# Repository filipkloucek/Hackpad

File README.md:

# Hackpad

- Just followed hackclub's guided tutorial. It was really fun. Looking forward to make my own stuff :)

/ update // added a few extra things. Prolly gonna use this for Spotify

/ update 2 // Completely new design - realised i used a wrong display. But it looks even better now
  
/ firmware made by AI for now. I can'T code but gonna learn that too. 

Used parts: 

- 5x Cherry MX Switches
- 1x SK6812 MINI Led
- 1x XIAO RP2040
- 5x Blank DSA Keycaps
- 4x M3x16 Bolt
- 4x M3 Heatset
- 1x EC11 Rotary encoder
- 1x 0.91 inch OLED display (SDD1306 OLED) 

Files: 

- KMK Firmware (main.py) 
- HACKPAD V3 (HACKPAD - BOTTOM - V3,HACKPAD - TOP - V3,HACKPAD - PCB - V3)

PCB

SCHEMATIC

CASE

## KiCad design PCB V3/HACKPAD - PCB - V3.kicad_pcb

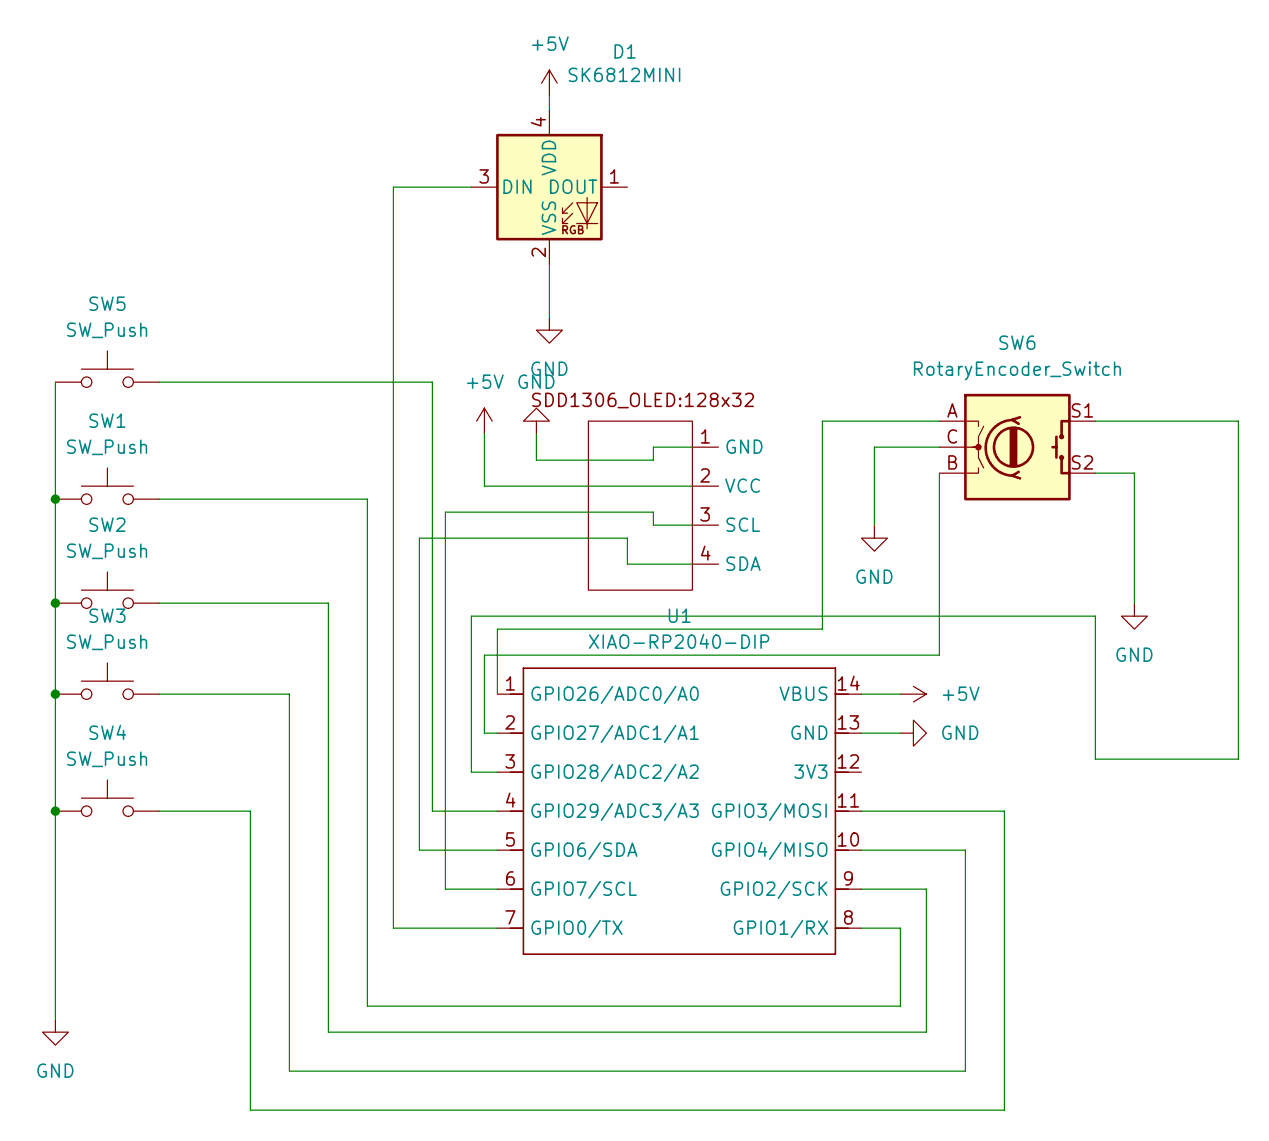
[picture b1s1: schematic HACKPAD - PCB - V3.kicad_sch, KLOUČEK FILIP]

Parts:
D1: SK6812MINI; LED_SK6812MINI_PLCC4_3.5x3.5mm_P1.75mm
DS1: SSD1306-0.91-OLED-4pin-128x32
SW1, SW2, SW3, SW4, SW5: SW_Push; SW_Cherry_MX_1.00u_PCB
SW6: RotaryEncoder_Switch; RotaryEncoder_Alps_EC11E-Switch_Vertical_H20mm
U1: XIAO-RP2040-DIP; MOUDLE14P-XIAO-DIP-SMD

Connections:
+5V: D1.4 (VDD), DS1.2 (VCC), U1.14 (VBUS)
GND: D1.2 (VSS), DS1.1 (GND), SW1.1, SW2.1, SW3.1, SW4.1, SW5.1, SW6.C, SW6.S2, U1.13 (GND)
unnamed: D1.3 (DIN), U1.7 (GPIO0/TX)
unnamed: DS1.3 (SCL), U1.6 (GPIO7/SCL)
unnamed: DS1.4 (SDA), U1.5 (GPIO6/SDA)
unnamed: SW1.2, U1.8 (GPIO1/RX)
unnamed: SW2.2, U1.9 (GPIO2/SCK)
unnamed: SW4.2, U1.11 (GPIO3/MOSI)
unnamed: SW3.2, U1.10 (GPIO4/MISO)
unnamed: SW6.A, U1.1 (GPIO26/ADC0/A0)
unnamed: SW6.B, U1.2 (GPIO27/ADC1/A1)
unnamed: SW6.S1, U1.3 (GPIO28/ADC2/A2)
unnamed: SW5.2, U1.4 (GPIO29/ADC3/A3)

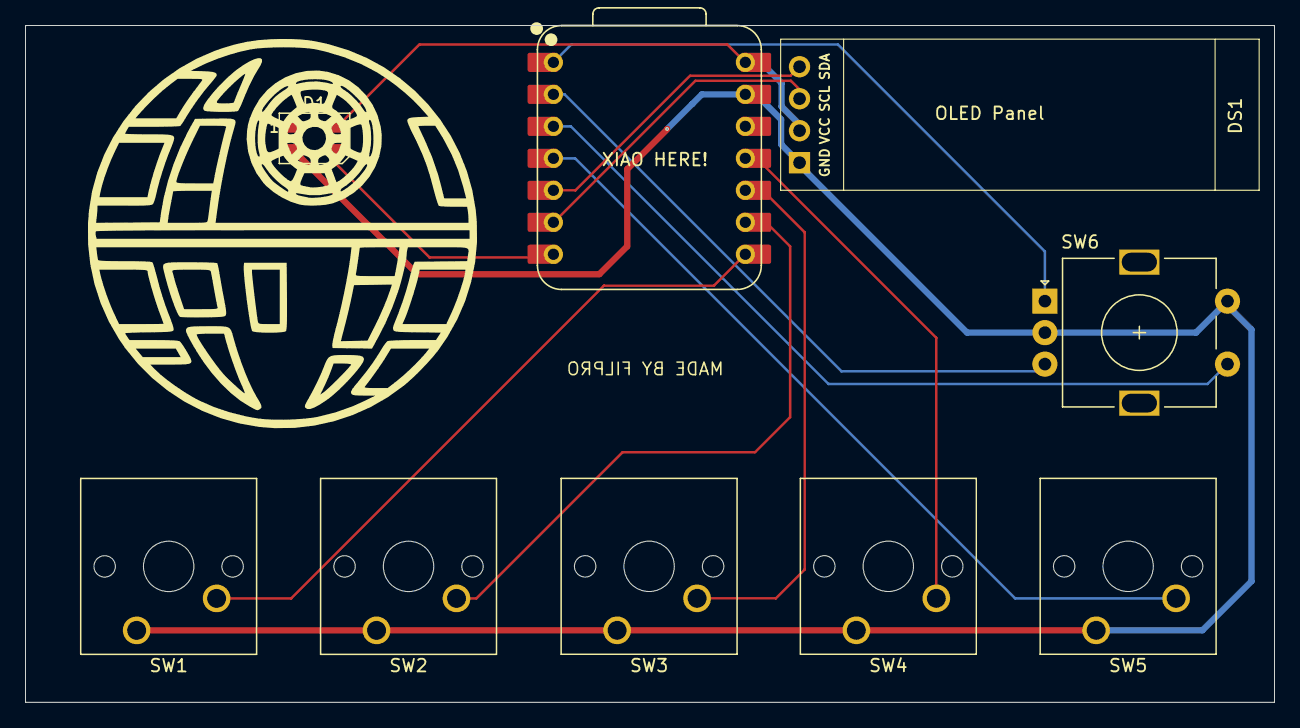
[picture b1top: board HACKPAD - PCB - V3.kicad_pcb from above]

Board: 2 copper layers, 99.2 x 53.7 mm, 10 parts (0 on the bottom side), 13 nets.

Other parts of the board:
D: LOGO

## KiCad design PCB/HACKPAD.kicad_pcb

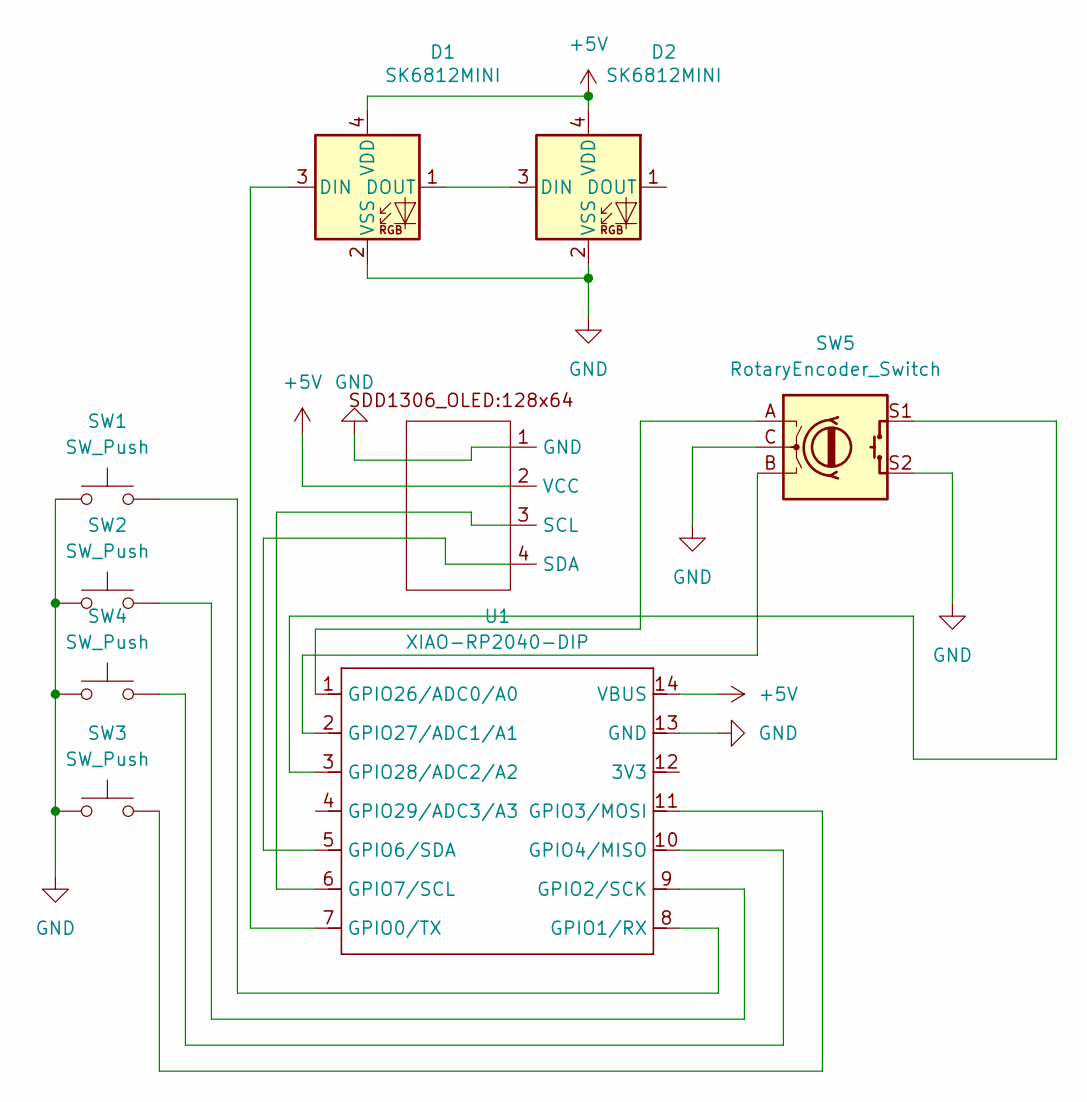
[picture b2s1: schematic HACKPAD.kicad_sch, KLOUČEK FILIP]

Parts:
D1, D2: SK6812MINI; LED_SK6812MINI_PLCC4_3.5x3.5mm_P1.75mm
DS1: 128x64OLED
SW1, SW2, SW3, SW4: SW_Push; SW_Cherry_MX_1.00u_PCB
SW5: RotaryEncoder_Switch; RotaryEncoder_Alps_EC11E-Switch_Vertical_H20mm
U1: XIAO-RP2040-DIP; MOUDLE14P-XIAO-DIP-SMD

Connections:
+5V: D1.4 (VDD), D2.4 (VDD), DS1.2 (VCC), U1.14 (VBUS)
GND: D1.2 (VSS), D2.2 (VSS), DS1.1 (GND), SW1.1, SW2.1, SW3.1, SW4.1, SW5.C, SW5.S2, U1.13 (GND)
unnamed: D1.3 (DIN), U1.7 (GPIO0/TX)
unnamed: D1.1 (DOUT), D2.3 (DIN)
unnamed: DS1.3 (SCL), U1.6 (GPIO7/SCL)
unnamed: DS1.4 (SDA), U1.5 (GPIO6/SDA)
unnamed: SW1.2, U1.8 (GPIO1/RX)
unnamed: SW2.2, U1.9 (GPIO2/SCK)
unnamed: SW3.2, U1.11 (GPIO3/MOSI)
unnamed: SW4.2, U1.10 (GPIO4/MISO)
unnamed: SW5.A, U1.1 (GPIO26/ADC0/A0)
unnamed: SW5.B, U1.2 (GPIO27/ADC1/A1)
unnamed: SW5.S1, U1.3 (GPIO28/ADC2/A2)

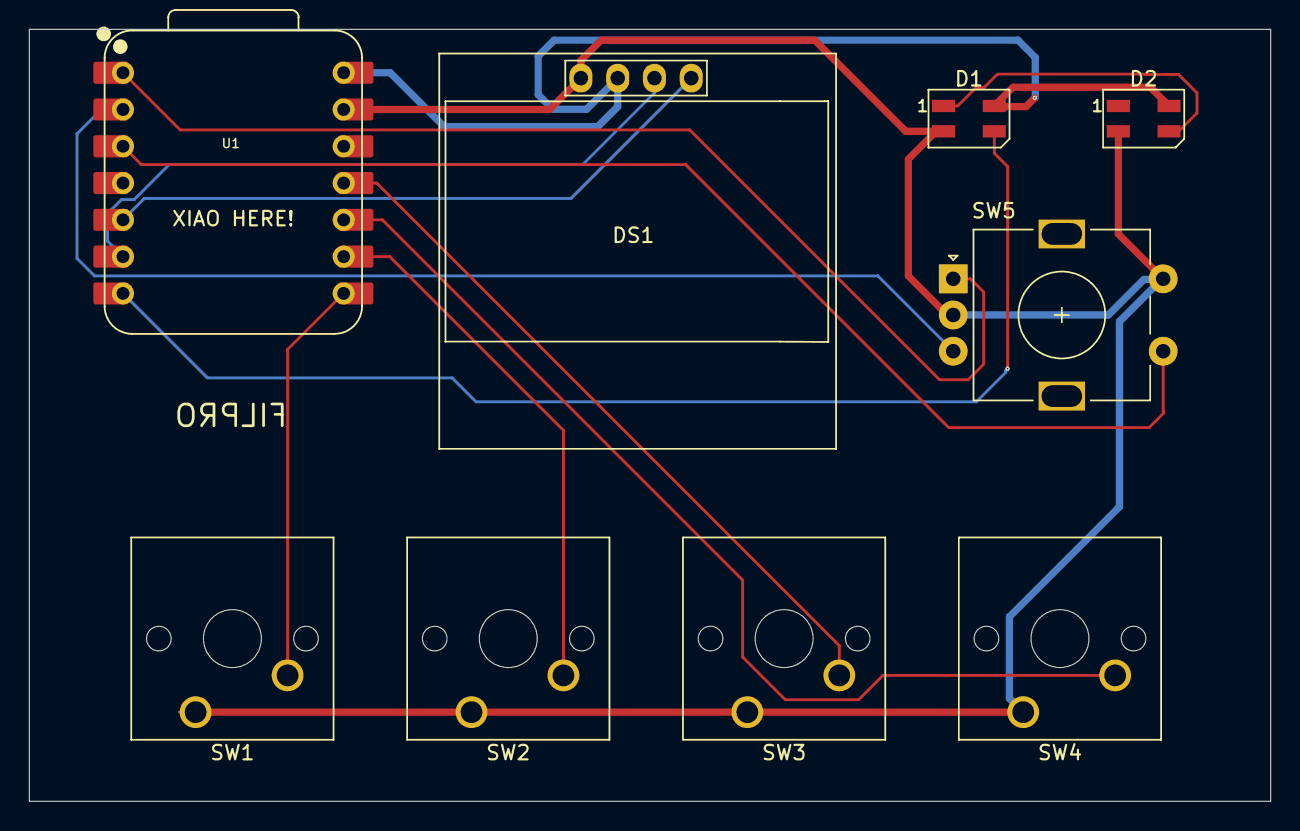
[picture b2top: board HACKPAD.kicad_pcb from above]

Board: 2 copper layers, 85.7 x 53.3 mm, 9 parts (0 on the bottom side), 13 nets.

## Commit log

2025-12-26 README.md
